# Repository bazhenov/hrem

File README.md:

# HREM

This project contains firware code and KiCad schematics/PCB files for simple door latch reminder.

## The problem

Me and my wife forget to close our flat entrance door from time to time. What will you do about that? :)

This project is simple hardware solution to remind us about open door. It's not the simplest nor most elegant solution, but more like excuse for practicing skills in embedded software development and electrical engineering.

## The solution

Solution is quite simple:

1. door latch has magnet on it's end;
1. hall effect sensor integrated into door frame right near latch with magnet;
1. μC powering up hall sensor once in a while and check magnet presense (hence door is closed);
1. buzzer goes on if latch is open.

## Part list

Complete BOM is in project files, but here are key parts used in a project:

1. [ATTiny85] as a μC
1. [Honeywell SS49][SS19] hall effect sensor;
1. [HT7733] as a voltage boost up controller. Single AAA battery is required.

## Building firmware

You need to have standart AVR toolchain is installed (e.g. `avr-gcc`, `avr-objcopy`...). Beyond that building firmware is as simple as:

```
$ make
```

[SS19]: https://eu.mouser.com/datasheet/2/187/SS49-1168552.pdf
[HT7733]: https://img.ozdisan.com/ETicaret_Dosya/349361_8060324.pdf
[attiny85]: https://ww1.microchip.com/downloads/en/DeviceDoc/Atmel-2586-AVR-8-bit-Microcontroller-ATtiny25-ATtiny45-ATtiny85_Datasheet.pdf

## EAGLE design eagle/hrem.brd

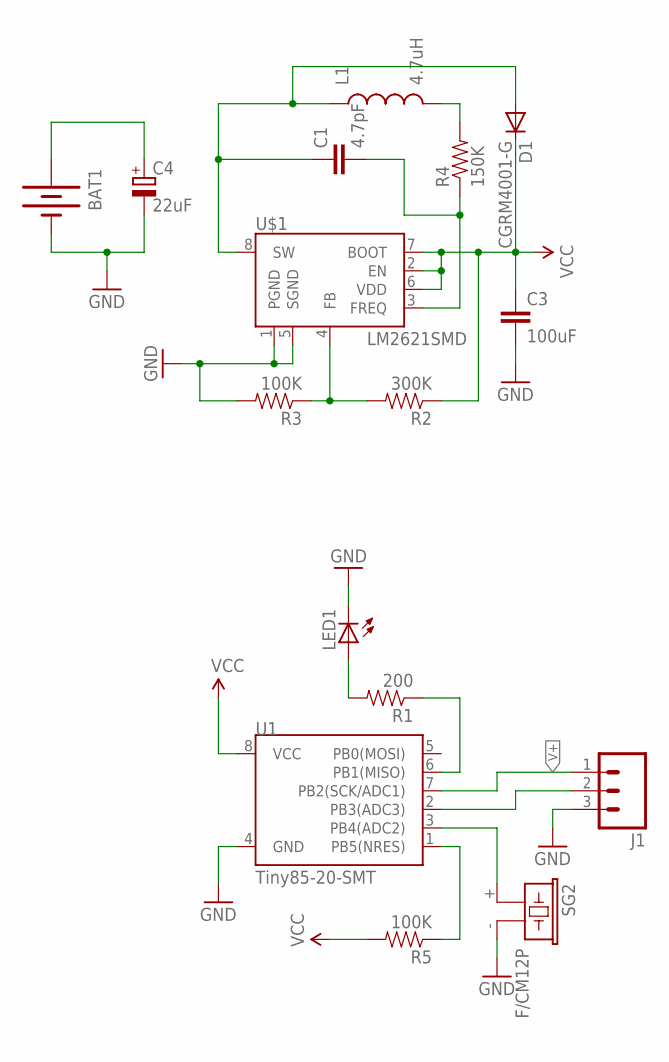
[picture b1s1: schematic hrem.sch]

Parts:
BAT1: BATTERYAAA; BATTERY-AAA
C1: 4.7pF; C1206
C3: 100uF; C1206
C4: 22uF; E2,5-5
D1: CGRM4001-G; SOD-123_MINI-SMA
J1: M03PTH; 1X03
L1: 4.7uH; CR54
LED1: LED3MM
R1: 200; 1206
R2: 300K; 1206
R3, R5: 100K; 1206
R4: 150K; 1206
SG2: F/CM12P
U1: Tiny85-20-SMT; SO08-EIAJ
U$1: LM2621SMD; MSOP-8

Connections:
GND: BAT1.GND@1 (-), C3.2, C4.-, J1.3, LED1.K (C), R3.2, SG2.- (2), U1.4 (GND), U$1.1 (PGND), U$1.5 (SGND)
unnamed: LED1.A, R1.2
unnamed: R5.1, U1.1 (PB5(NRES))
unnamed: SG2.+ (1), U1.3 (PB4(ADC2))
unnamed: J1.2, U1.2 (PB3(ADC3))
unnamed: R1.1, U1.6 (PB1(MISO))
unnamed: C1.1, D1.A, L1.P$1 (1), U$1.8 (SW)
unnamed: L1.P$2 (2), R4.2
unnamed: C1.2, R4.1, U$1.3 (FREQ)
unnamed: R2.2, R3.1, U$1.4 (FB)
unnamed: BAT1.PWR@1 (+), C4.+
V+: J1.1, U1.7 (PB2(SCK/ADC1))
VCC: C3.1, D1.C, R2.1, R5.2, U1.8 (VCC), U$1.2 (EN), U$1.6 (VDD), U$1.7 (BOOT)

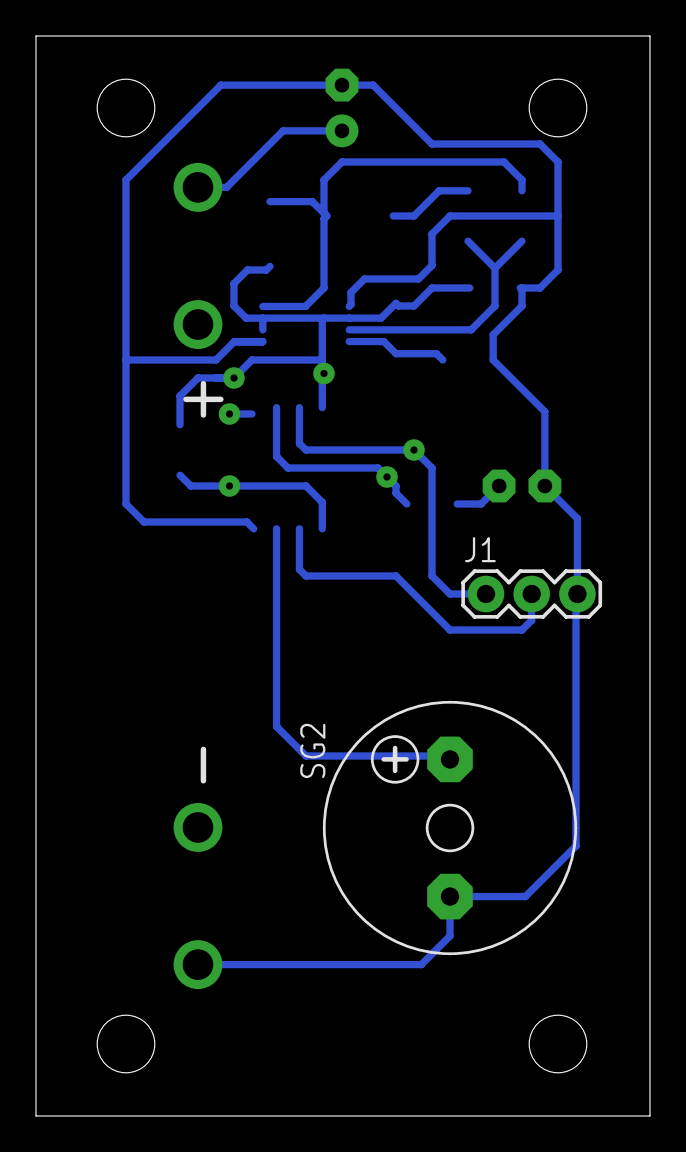
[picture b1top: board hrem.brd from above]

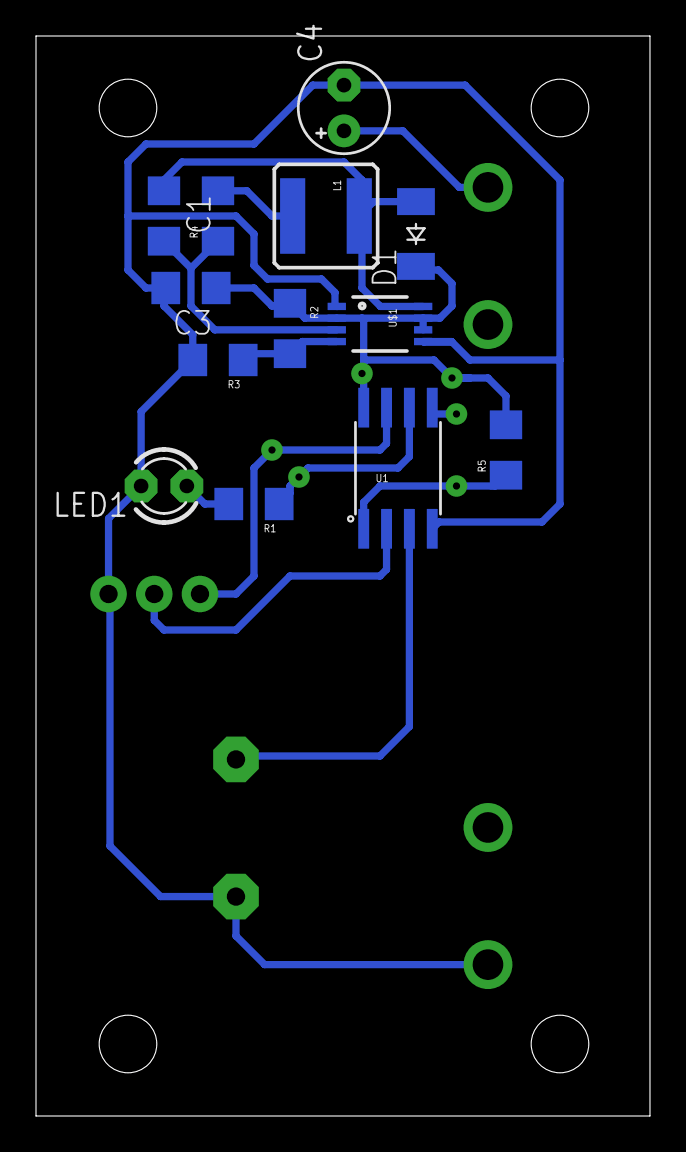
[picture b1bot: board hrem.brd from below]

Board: 2 copper layers, 34.1 x 60.0 mm, 16 parts (13 on the bottom side), 13 nets.

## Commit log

2016-03-14 Первая рабочая версия
2016-03-14 Добавил bin/hex файлы в gitignore
2016-03-14 Поддержка индикаторного светодиода
2016-03-15 Sleep mode added
2016-03-31 Первый рабочий прототип
2016-03-31 Удалил ненужные файлы
2016-05-02 PCB improvements
2016-06-19 SMD version
2016-10-23 Project canges
2019-10-12 prototype of new version is commited
2019-10-19 hardware changes
2019-10-26 Some changes to schematics
2019-11-23 Makefile now correctly tracks source changes
2019-11-23 Enabled INT0
2019-11-24 Using standart bit manipulating idioms rather than own macros
2019-11-24 New rev
2020-01-02 Migration to new KiCad version
2020-01-03 Added backup files under gitignore
2020-01-03 Update ICSP footprint information
2020-01-03 Moved to a cpp
2020-01-03 buzzer fixed
2020-01-05 Firmware size reporting added
2020-01-05 Moved to multibinary makefile using CPP
2020-01-05 Various imrovements
    - C++ templates are used to isolate pin management
    - flash-* targets are renamed to *.flash to improve shell experience
2020-01-05 LongPress implemented for Button
2020-01-06 Register acces functions moved to a separate struct
2020-01-06 DigitalOutput::strobe() method added
2020-01-06 Base poll loop implemented
2020-01-07 Template ompimizations
2020-01-09 Working version
2020-01-12 KiCad new footprints
2020-01-17 Footprint change
2020-01-19 Work over schematics
2020-01-19 Button footprint added
2020-01-19 Boosting voltage regulator pcb layout
2020-01-20 Buzzer and LED PCB layout
2020-02-01 Work on PCB layout
2020-02-01 PCB layout all set
2020-02-02 Buzzer PCB layout dimensions fixed
2020-02-02 PCB tracks cleanup
2020-02-02 Replace 68R with 100R on LED for component unification purposes (15mA current)
2020-02-02 PCB POWER trace for BZ1 and D2
2020-02-02 Decoupling caps added on U3 and U4
2020-02-02 Schematic cleanup
2020-02-02 Revision updated on shcematics
2020-02-02 PCB ref names positioning and vendor part names
2020-02-09 First fabrication version
2020-03-16 simavr emulation toolchain added
2020-04-17 Fixed layout issue
    Q1 has invalid schematics symbol. Base and collector was swaped.
2020-04-18 Remove old files
2020-04-18 README added
2020-04-18 Firmware building instructions added
2020-04-18 Create LICENSE
2020-04-18 Testing GHA
2020-04-18 Implementing GitHub Actions
    https://github.com/marketplace/actions/avr-make is used as build action
2020-04-18 Update README.md
    Add CI status badge
2020-04-18 Rename workflow
2020-04-18 Update CI-badge
2020-04-18 Publishing firmware artifacts to GHA (#2)
    * Update main.yml
    * Rename workflow
    * Update CI-badge
2020-04-18 typo

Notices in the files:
parts and their libraries:
SparkFun-Connectors: Licensing: Creative Commons ShareAlike 4.0 International - https://creativecommons.org/licenses/by-sa/4.0
